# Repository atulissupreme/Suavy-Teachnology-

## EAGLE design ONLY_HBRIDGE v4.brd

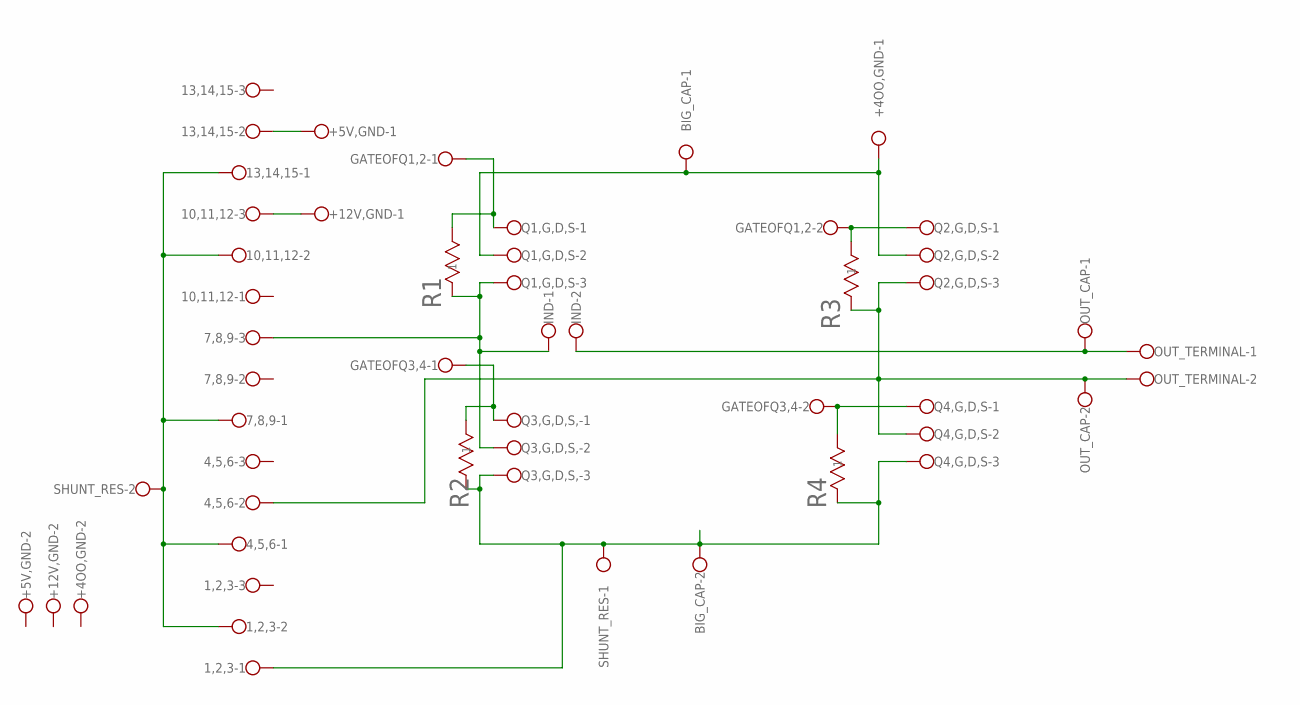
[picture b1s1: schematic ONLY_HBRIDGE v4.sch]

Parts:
1,2,3, 4,5,6, 7,8,9, 10,11,12, 13,14,15: W237-03P; W237-133
+4OO,GND, +5V,GND, +12V,GND: W237-02P; W237-132
BIG_CAP: W237-02P; W237-132
GATEOFQ1,2, GATEOFQ3,4: W237-02P; W237-132
IND: W237-02P; W237-132
OUT_CAP: W237-02P; W237-132
OUT_TERMINAL: W237-02P; W237-132
Q1,G,D,S, Q2,G,D,S, Q3,G,D,S,, Q4,G,D,S: W237-03P; W237-133
R1, R2, R3, R4: CF14JT10K0STA_CF14_STP; STA_CF14_STP
SHUNT_RES: W237-02P; W237-132

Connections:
unnamed: GATEOFQ1,2.1, Q1,G,D,S.1, R1.2
unnamed: GATEOFQ1,2.2, Q2,G,D,S.1, R3.1
unnamed: 1,2,3.2, 4,5,6.1, 7,8,9.1, 10,11,12.2, 13,14,15.1, SHUNT_RES.2
unnamed: GATEOFQ3,4.2, Q4,G,D,S.1, R4.1
unnamed: GATEOFQ3,4.1, Q3,G,D,S,.1, R2.1
unnamed: 1,2,3.1, BIG_CAP.2, Q3,G,D,S,.3, Q4,G,D,S.3, R2.2, R4.2, SHUNT_RES.1
unnamed: 13,14,15.2, +5V,GND.1
unnamed: 10,11,12.3, +12V,GND.1
unnamed: +4OO,GND.1, BIG_CAP.1, Q1,G,D,S.2, Q2,G,D,S.2
unnamed: 7,8,9.3, IND.1, Q1,G,D,S.3, Q3,G,D,S,.2, R1.1
unnamed: IND.2, OUT_CAP.1, OUT_TERMINAL.1
unnamed: 4,5,6.2, OUT_CAP.2, OUT_TERMINAL.2, Q2,G,D,S.3, Q4,G,D,S.2, R3.2

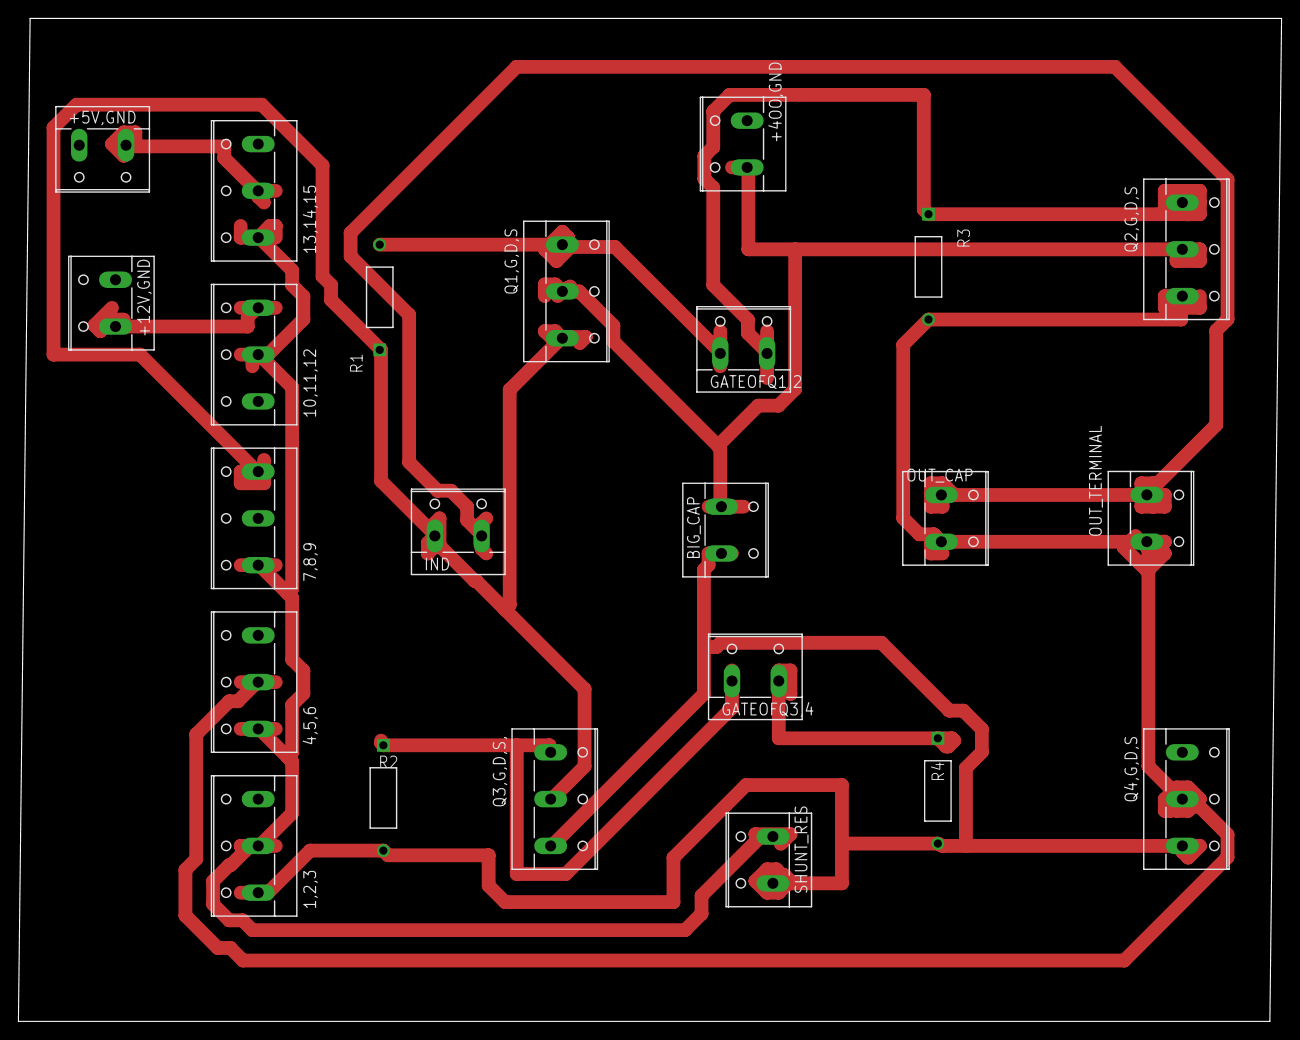
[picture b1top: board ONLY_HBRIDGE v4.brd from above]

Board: 2 copper layers, 137.1 x 108.9 mm, 23 parts (0 on the bottom side), 12 nets.

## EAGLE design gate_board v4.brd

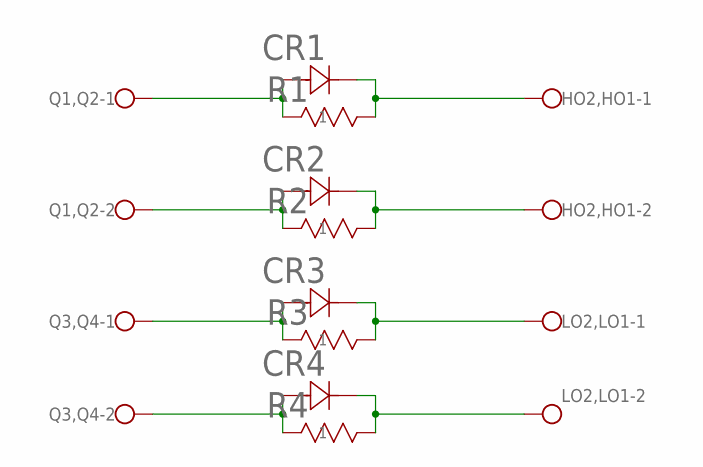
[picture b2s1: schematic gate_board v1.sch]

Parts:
CR1, CR2, CR3, CR4: 1N4007CR_1N4005_ONS; CR_1N4005_ONS
HO2,HO1: W237-02P; W237-132
LO2,LO1: W237-02P; W237-132
Q1,Q2, Q3,Q4: W237-02P; W237-132
R1, R2, R3, R4: CF14JT10K0STA_CF14_STP; STA_CF14_STP

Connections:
unnamed: CR1.2, Q1,Q2.1, R1.1
unnamed: CR1.1, HO2,HO1.1, R1.2
unnamed: CR2.2, Q1,Q2.2, R2.1
unnamed: CR2.1, HO2,HO1.2, R2.2
unnamed: CR3.2, Q3,Q4.1, R3.1
unnamed: CR3.1, LO2,LO1.1, R3.2
unnamed: CR4.2, Q3,Q4.2, R4.1
unnamed: CR4.1, LO2,LO1.2, R4.2

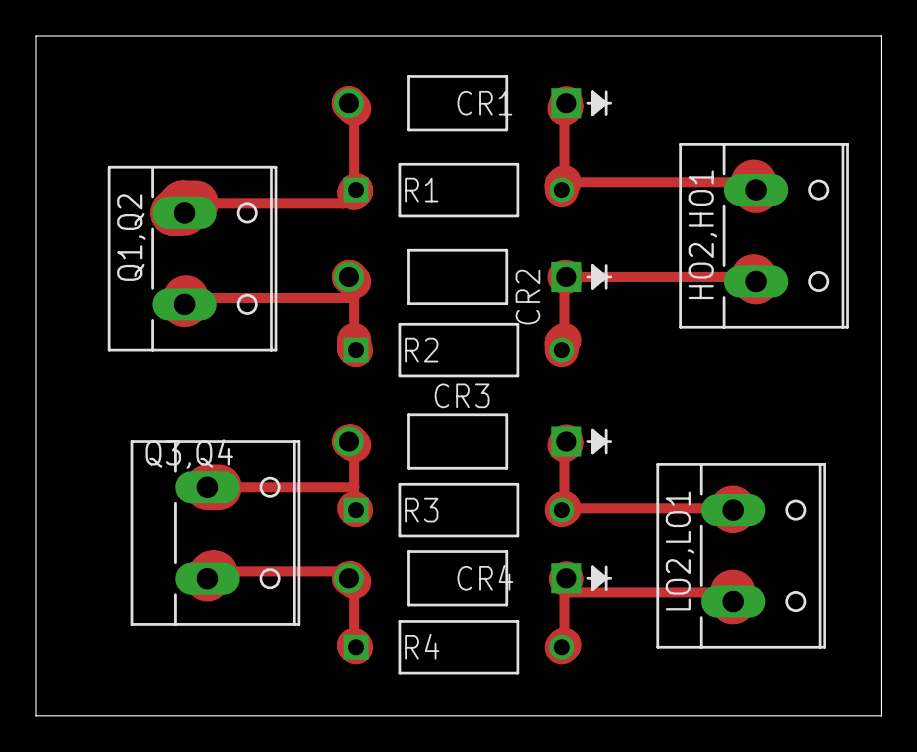
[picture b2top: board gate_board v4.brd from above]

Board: 2 copper layers, 47.0 x 37.8 mm, 12 parts (0 on the bottom side), 8 nets.

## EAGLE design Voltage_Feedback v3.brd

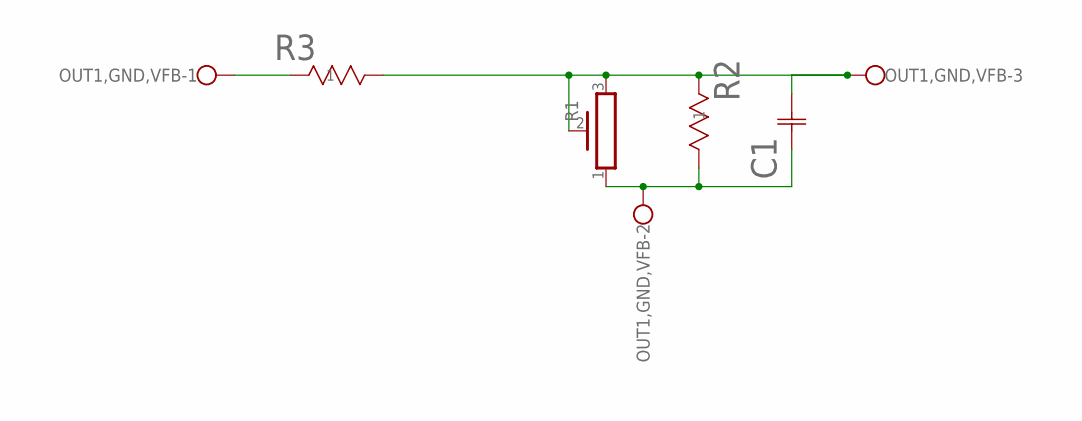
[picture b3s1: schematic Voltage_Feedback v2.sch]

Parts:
C1: 564R60GAD10CAP_60GAD10_VIS; CAP_60GAD10_VIS
OUT1,GND,VFB: W237-03P; W237-133
R1: PV36P
R2, R3: CF14JT10K0STA_CF14_STP; STA_CF14_STP

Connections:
unnamed: OUT1,GND,VFB.1, R3.1
unnamed: C1.2, OUT1,GND,VFB.3, R1.2, R1.3, R2.1, R3.2
unnamed: C1.1, OUT1,GND,VFB.2, R1.1, R2.2

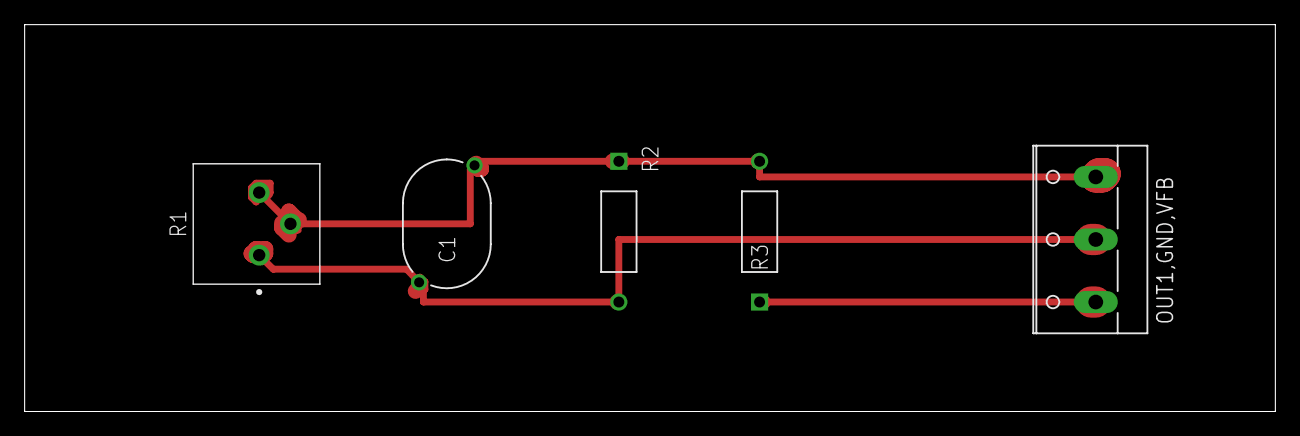
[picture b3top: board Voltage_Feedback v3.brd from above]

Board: 2 copper layers, 101.6 x 31.4 mm, 5 parts (0 on the bottom side), 3 nets.

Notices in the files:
parts and their libraries:
COPYRIGHT: Copyright (C) 2024 Ultra Librarian. All rights reserved.
